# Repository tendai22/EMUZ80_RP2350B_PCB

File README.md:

# EMUZ80_RP2350B_PCB

KiCad PCB for EMUZ80 for WeAct RP2350B CoreBoard

## What is this.

RP2350B CoreBoard ベースの Z80 基板を手配線で作成し、ソフトを開発してきたが、そろそろ使い方が固まってきたので、RP2350B Core Board ベースで8bit CPU 駆動ソフト開発用の基板を作れそうな気がしたので、基板を1枚起こした。

6502駆動のために、メモリマップドI/Oのためのアドレスデコードも試そうと、GPIO16 に WAIT を割り当て、その上3本を空けてある。ファームがまだできていないので検証はまだだが、多分大丈夫。

AE-RP2040 基板で搭載した、ジャンパ飛ばし端子は用意できなかった。既存のメザニン基板をそのまま使うことは多分難しいだろう。

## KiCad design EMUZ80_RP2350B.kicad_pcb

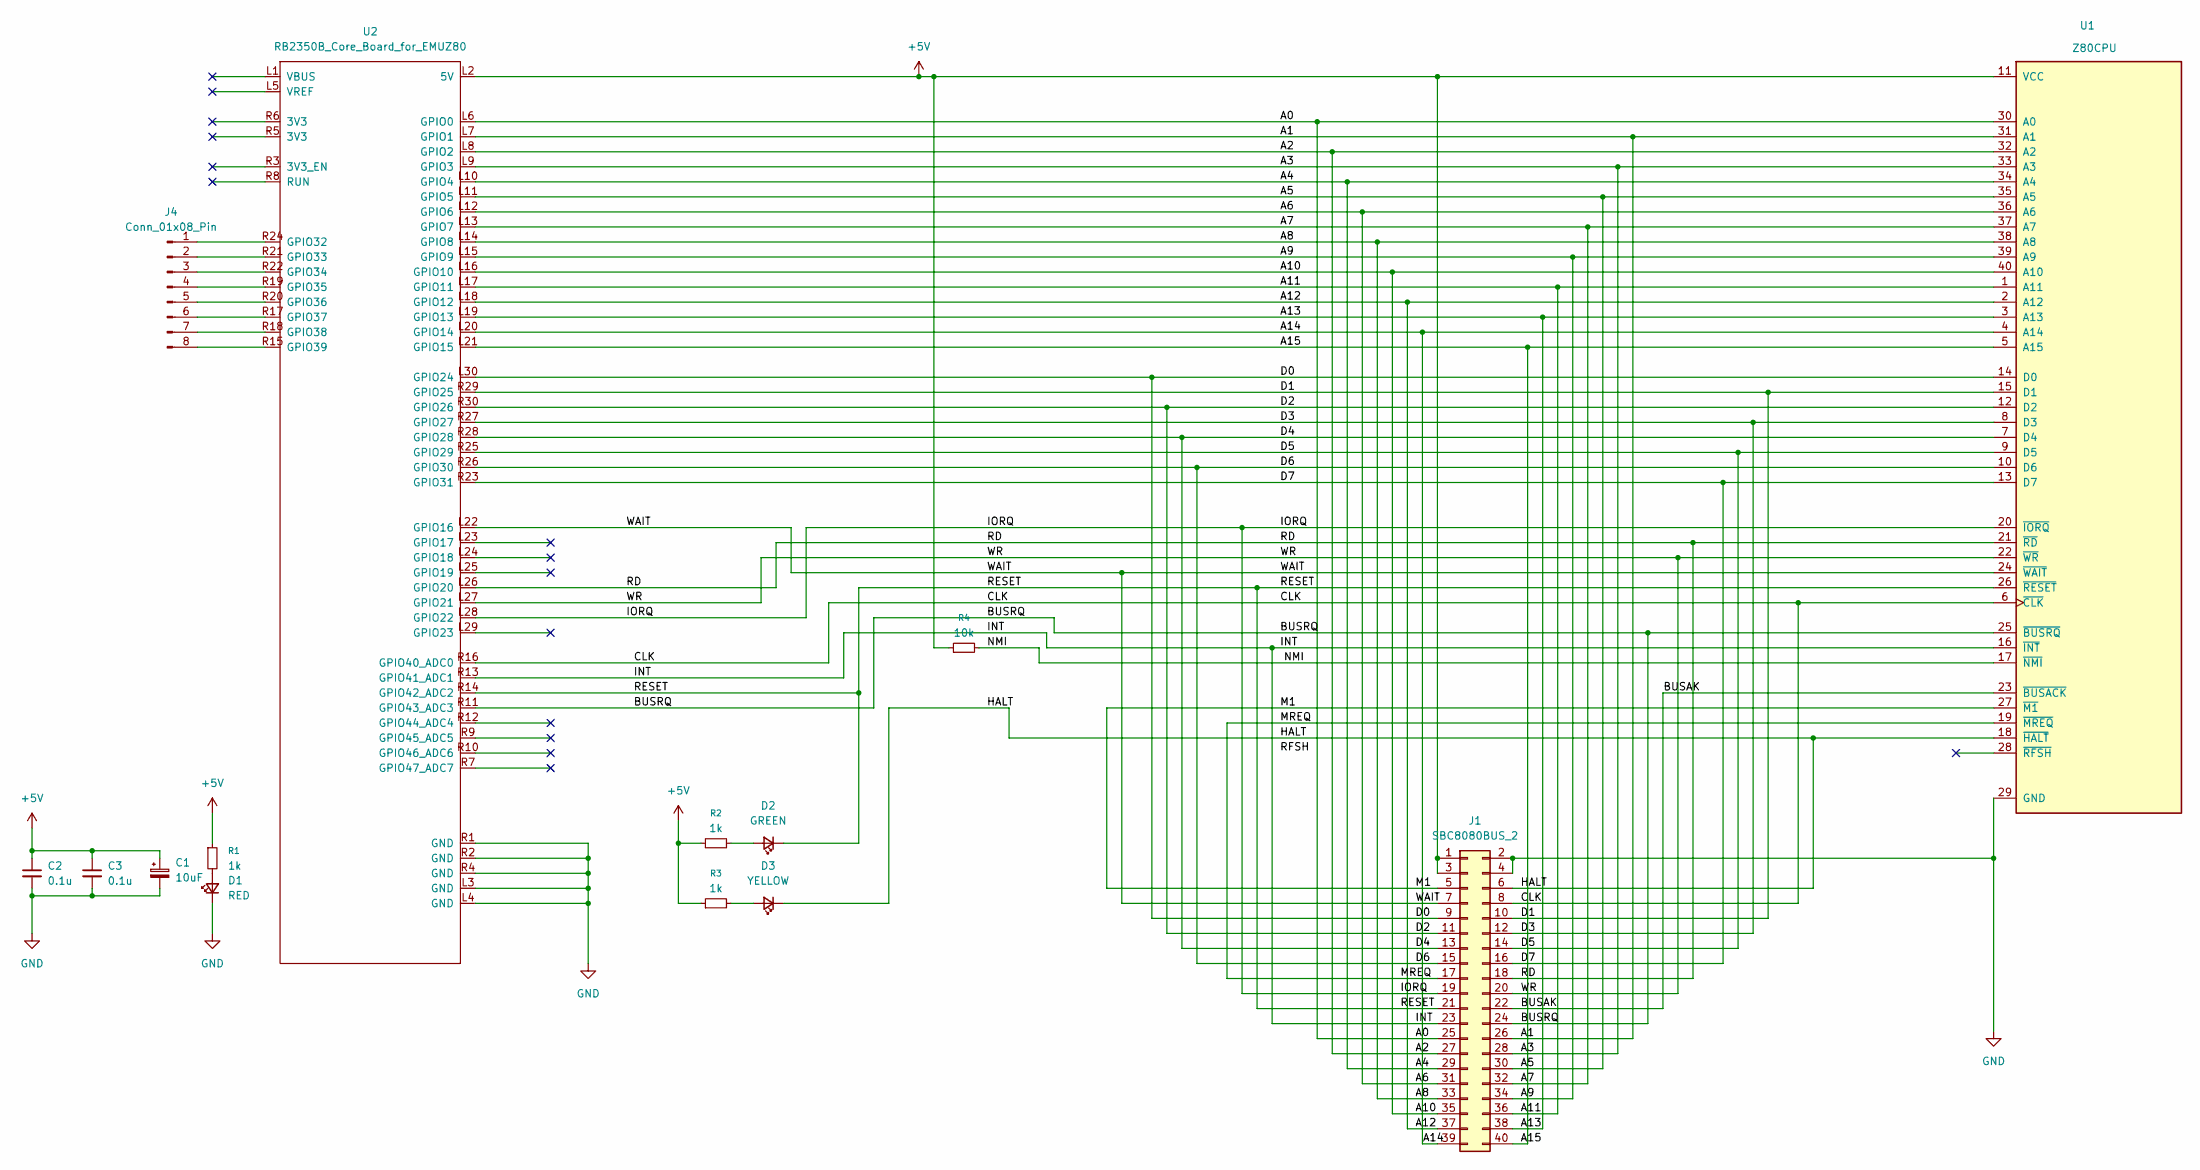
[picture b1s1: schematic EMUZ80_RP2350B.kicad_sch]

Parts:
C1: 10uF; CP_Radial_D5.0mm_P2.50mm
C2, C3: 0.1u; C_Disc_D3.0mm_W1.6mm_P2.50mm
D1: RED; LED_D3.0mm
D2: GREEN; LED_D3.0mm
D3: YELLOW; LED_D3.0mm
J1: SBC8080BUS_2; PinSocket_2x20_OvalPad
J4: Conn_01x08_Pin; PinHeader_1x08_P2.54mm_Vertical
R1, R2, R3: 1k; R_Axial_L5.5mm_D2.0mm_P7.62mm_Horizontal
R4: 10k; R_Axial_L5.5mm_D2.0mm_P7.62mm_Horizontal
U1: Z80CPU; DIP-40_SidePin_Z80
U2: RB2350B_Core_Board_for_EMUZ80; RB2350B_Core_Board

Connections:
+5V: C1.1, C2.1, C3.1, J1.1 (5V), J1.3 (5V), R1.1, R2.1, R3.1, R4.1, U1.11 (VCC), U2.L2 (5V)
/A0: J1.25 (A0), U1.30 (A0), U2.L6 (GPIO0)
/A1: J1.26 (A1), U1.31 (A1), U2.L7 (GPIO1)
/A2: J1.27 (A2), U1.32 (A2), U2.L8 (GPIO2)
/A3: J1.28 (A3), U1.33 (A3), U2.L9 (GPIO3)
/A4: J1.29 (A4), U1.34 (A4), U2.L10 (GPIO4)
/A5: J1.30 (A5), U1.35 (A5), U2.L11 (GPIO5)
/A6: J1.31 (A6), U1.36 (A6), U2.L12 (GPIO6)
/A7: J1.32 (A7), U1.37 (A7), U2.L13 (GPIO7)
/A8: J1.33 (A8), U1.38 (A8), U2.L14 (GPIO8)
/A9: J1.34 (A9), U1.39 (A9), U2.L15 (GPIO9)
/A10: J1.35 (A10), U1.40 (A10), U2.L16 (GPIO10)
/A11: J1.36 (A11), U1.1 (A11), U2.L17 (GPIO11)
/A12: J1.37 (A12), U1.2 (A12), U2.L18 (GPIO12)
/A13: J1.38 (A13), U1.3 (A13), U2.L19 (GPIO13)
/A14: J1.39 (A14), U1.4 (A14), U2.L20 (GPIO14)
/A15: J1.40 (A15), U1.5 (A15), U2.L21 (GPIO15)
/BUSAK: J1.22 (BUSAK), U1.23 (~BUSACK)
/BUSRQ: J1.24 (BUSRQ), U1.25 (~BUSRQ), U2.R11 (GPIO43_ADC3)
/CLK: J1.8 (CLK), U1.6 (~CLK), U2.R16 (GPIO40_ADC0)
/D0: J1.9 (D0), U1.14 (D0), U2.L30 (GPIO24)
/D1: J1.10 (D1), U1.15 (D1), U2.R29 (GPIO25)
/D2: J1.11 (D2), U1.12 (D2), U2.R30 (GPIO26)
/D3: J1.12 (D3), U1.8 (D3), U2.R27 (GPIO27)
/D4: J1.13 (D4), U1.7 (D4), U2.R28 (GPIO28)
/D5: J1.14 (D5), U1.9 (D5), U2.R25 (GPIO29)
/D6: J1.15 (D6), U1.10 (D6), U2.R26 (GPIO30)
/D7: J1.16 (D7), U1.13 (D7), U2.R23 (GPIO31)
/HALT: D3.1 (K), J1.6 (NC), U1.18 (~HALT)
/INT: J1.23 (INT), U1.16 (~INT), U2.R13 (GPIO41_ADC1)
/IORQ: J1.19 (IORQ), U1.20 (~IORQ), U2.L28 (GPIO22)
/M1: J1.5 (M1), U1.27 (~M1)
/MREQ: J1.17 (MREQ), U1.19 (~MREQ)
/NMI: R4.2, U1.17 (~NMI)
/RD: J1.18 (RD), U1.21 (~RD), U2.L26 (GPIO20)
/RESET: D2.1 (K), J1.21 (RESET), U1.26 (~RESET), U2.R14 (GPIO42_ADC2)
/WAIT: J1.7 (WAIT), U1.24 (~WAIT), U2.L22 (GPIO16)
/WR: J1.20 (WR), U1.22 (~WR), U2.L27 (GPIO21)
GND: C1.2, C2.2, C3.2, D1.1 (K), J1.2 (GND), J1.4 (GND), U1.29 (GND), U2.L3 (GND), U2.L4 (GND), U2.R1 (GND), U2.R2 (GND), U2.R4 (GND)
unnamed: D1.2 (A), R1.2
unnamed: D2.2 (A), R2.2
unnamed: D3.2 (A), R3.2
unnamed: J4.1, U2.R24 (GPIO32)
unnamed: J4.2, U2.R21 (GPIO33)
unnamed: J4.3, U2.R22 (GPIO34)
unnamed: J4.4, U2.R19 (GPIO35)
unnamed: J4.5, U2.R20 (GPIO36)
unnamed: J4.6, U2.R17 (GPIO37)
unnamed: J4.7, U2.R18 (GPIO38)
unnamed: J4.8, U2.R15 (GPIO39)

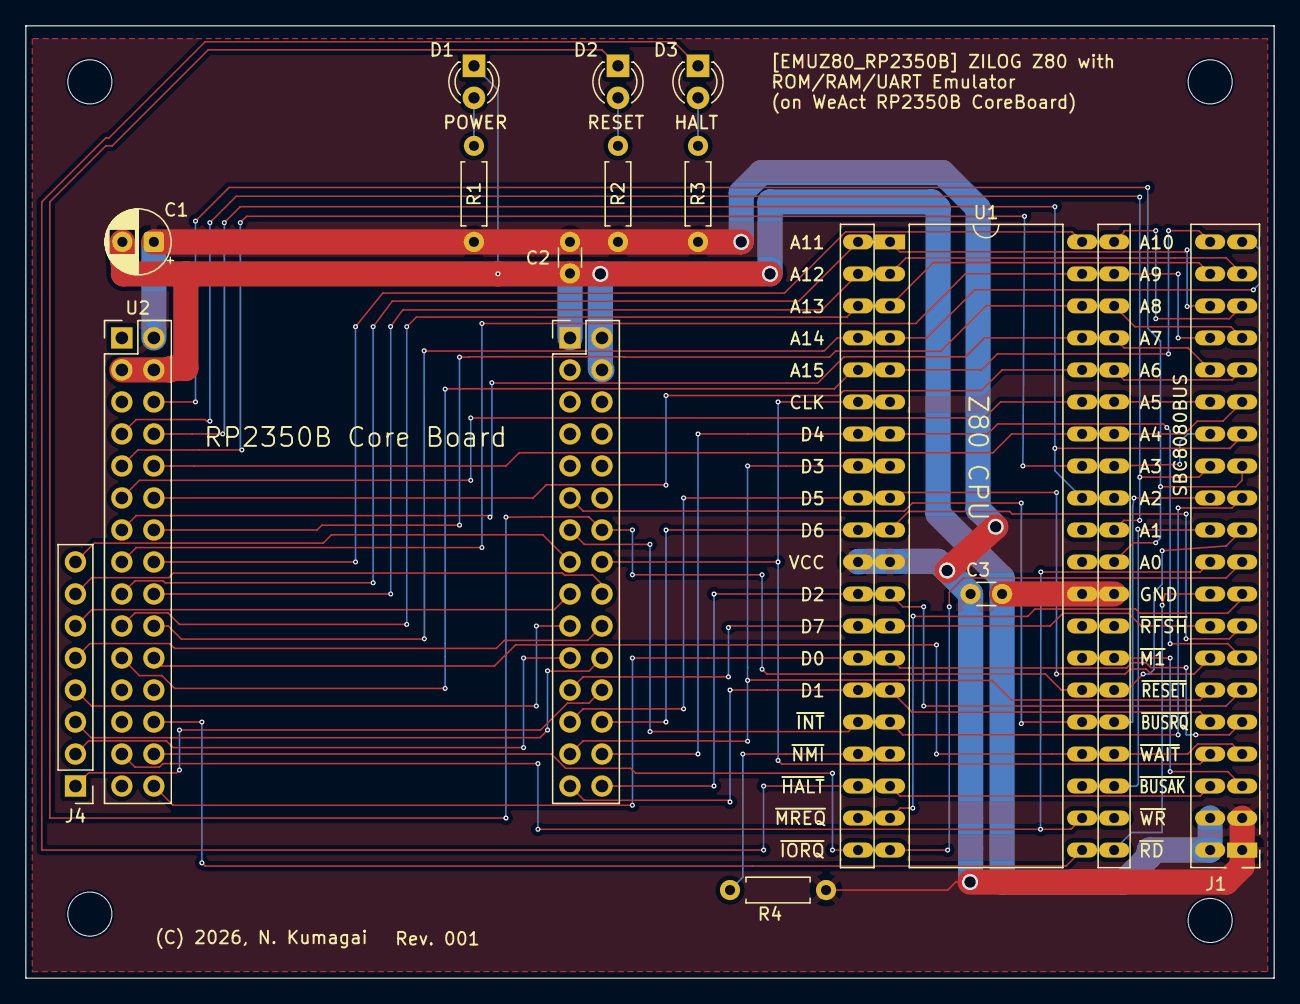
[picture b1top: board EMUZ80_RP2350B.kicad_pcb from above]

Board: 2 copper layers, 99.1 x 75.6 mm, 18 parts (0 on the bottom side), 50 nets.

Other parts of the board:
H1, H2, H3, H3#2: MountingHole; MountingHole_3.5mm

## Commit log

2026-02-09 main: Initial commit files, not yet PCBed
2026-02-09 main: add quite breaf text on README.md
2026-02-10 main: Rev001 almost be ready
2026-02-11 main: Rev001, ordered now

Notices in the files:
EMUZ80_RP2350B.kicad_pcb:
(C) 2026, N. Kumagai
